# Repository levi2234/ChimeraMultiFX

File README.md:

# ChimeraMultiFX

ChimeraMultiFX is a dual-MCU effects pedal platform. The Daisy Seed handles audio DSP while the ESP32 manages controls, Wi-Fi, and the browser-based UI.

## Repository layout

- [firmware/daisy](firmware/daisy) — Daisy Seed firmware built with libDaisy and DaisySP
- [firmware/esp32](firmware/esp32) — ESP32 control firmware and LittleFS web UI host
- [frontend](frontend) — Preact/Vite touch interface source
- [hardware/boards](hardware/boards) — KiCad PCB and schematic files
- [docs](docs) — repository notes and debugging write-ups

## Quick start

1. Review [firmware/daisy/README.md](firmware/daisy/README.md) for DSP build and flash steps.
2. Review [firmware/esp32/README.md](firmware/esp32/README.md) for ESP32 build, upload, and Wi-Fi setup.
3. Review [frontend/README.md](frontend/README.md) for local UI development.
4. Open [hardware/boards/daisyBoard.kicad_pro](hardware/boards/daisyBoard.kicad_pro) when working on hardware.

## Uploading code

- Daisy Seed: build with the Daisy make targets, then enter DFU bootloader mode and run the flashing command from [firmware/daisy/README.md](firmware/daisy/README.md).
- ESP32: build and upload from PlatformIO with the commands in [firmware/esp32/README.md](firmware/esp32/README.md).
- Frontend UI: build the web assets and upload them to the ESP32 filesystem using the steps in [frontend/README.md](frontend/README.md).

## Notes

- The ESP32 serves the built frontend from its LittleFS data partition.
- The Daisy and ESP32 communicate over UART; the ESP32 exposes a small HTTP/WebSocket bridge for the UI.

## License

MIT — see [LICENSE](LICENSE).

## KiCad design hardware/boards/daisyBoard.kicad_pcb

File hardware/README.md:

# Hardware Development

This directory contains all Electronic Design Automation (EDA) files, schematics, Bill of Materials (BOMs), and mechanical designs (enclosures, 3D models) for the ChimeraMultiFX pedal.

## Modular Board System

The hardware is designed to be modular and stackable:
- **`boards/audio-daisy/`**: The main audio DSP board housing the Daisy Seed.
- **`boards/control-esp32/`**: The controller board housing the ESP32 and inputs.
- **`boards/frontend-rpi/`**: The display driver board for the Raspberry Pi and 7" touchscreen.
- **`boards/power-supply/`**: Clean power delivery and distribution for the stack.

## Structure

- **`boards/`**: Contains the EDA project files (e.g., KiCad/Altium) as well as the exported PDF schematics for each specific PCB. Keeping the schematics in their respective board folders ensures that the design files and their documentation are tightly coupled.
- **`mechanical/`**: Contains STEP files, 3D models for the enclosure, and faceplate designs.

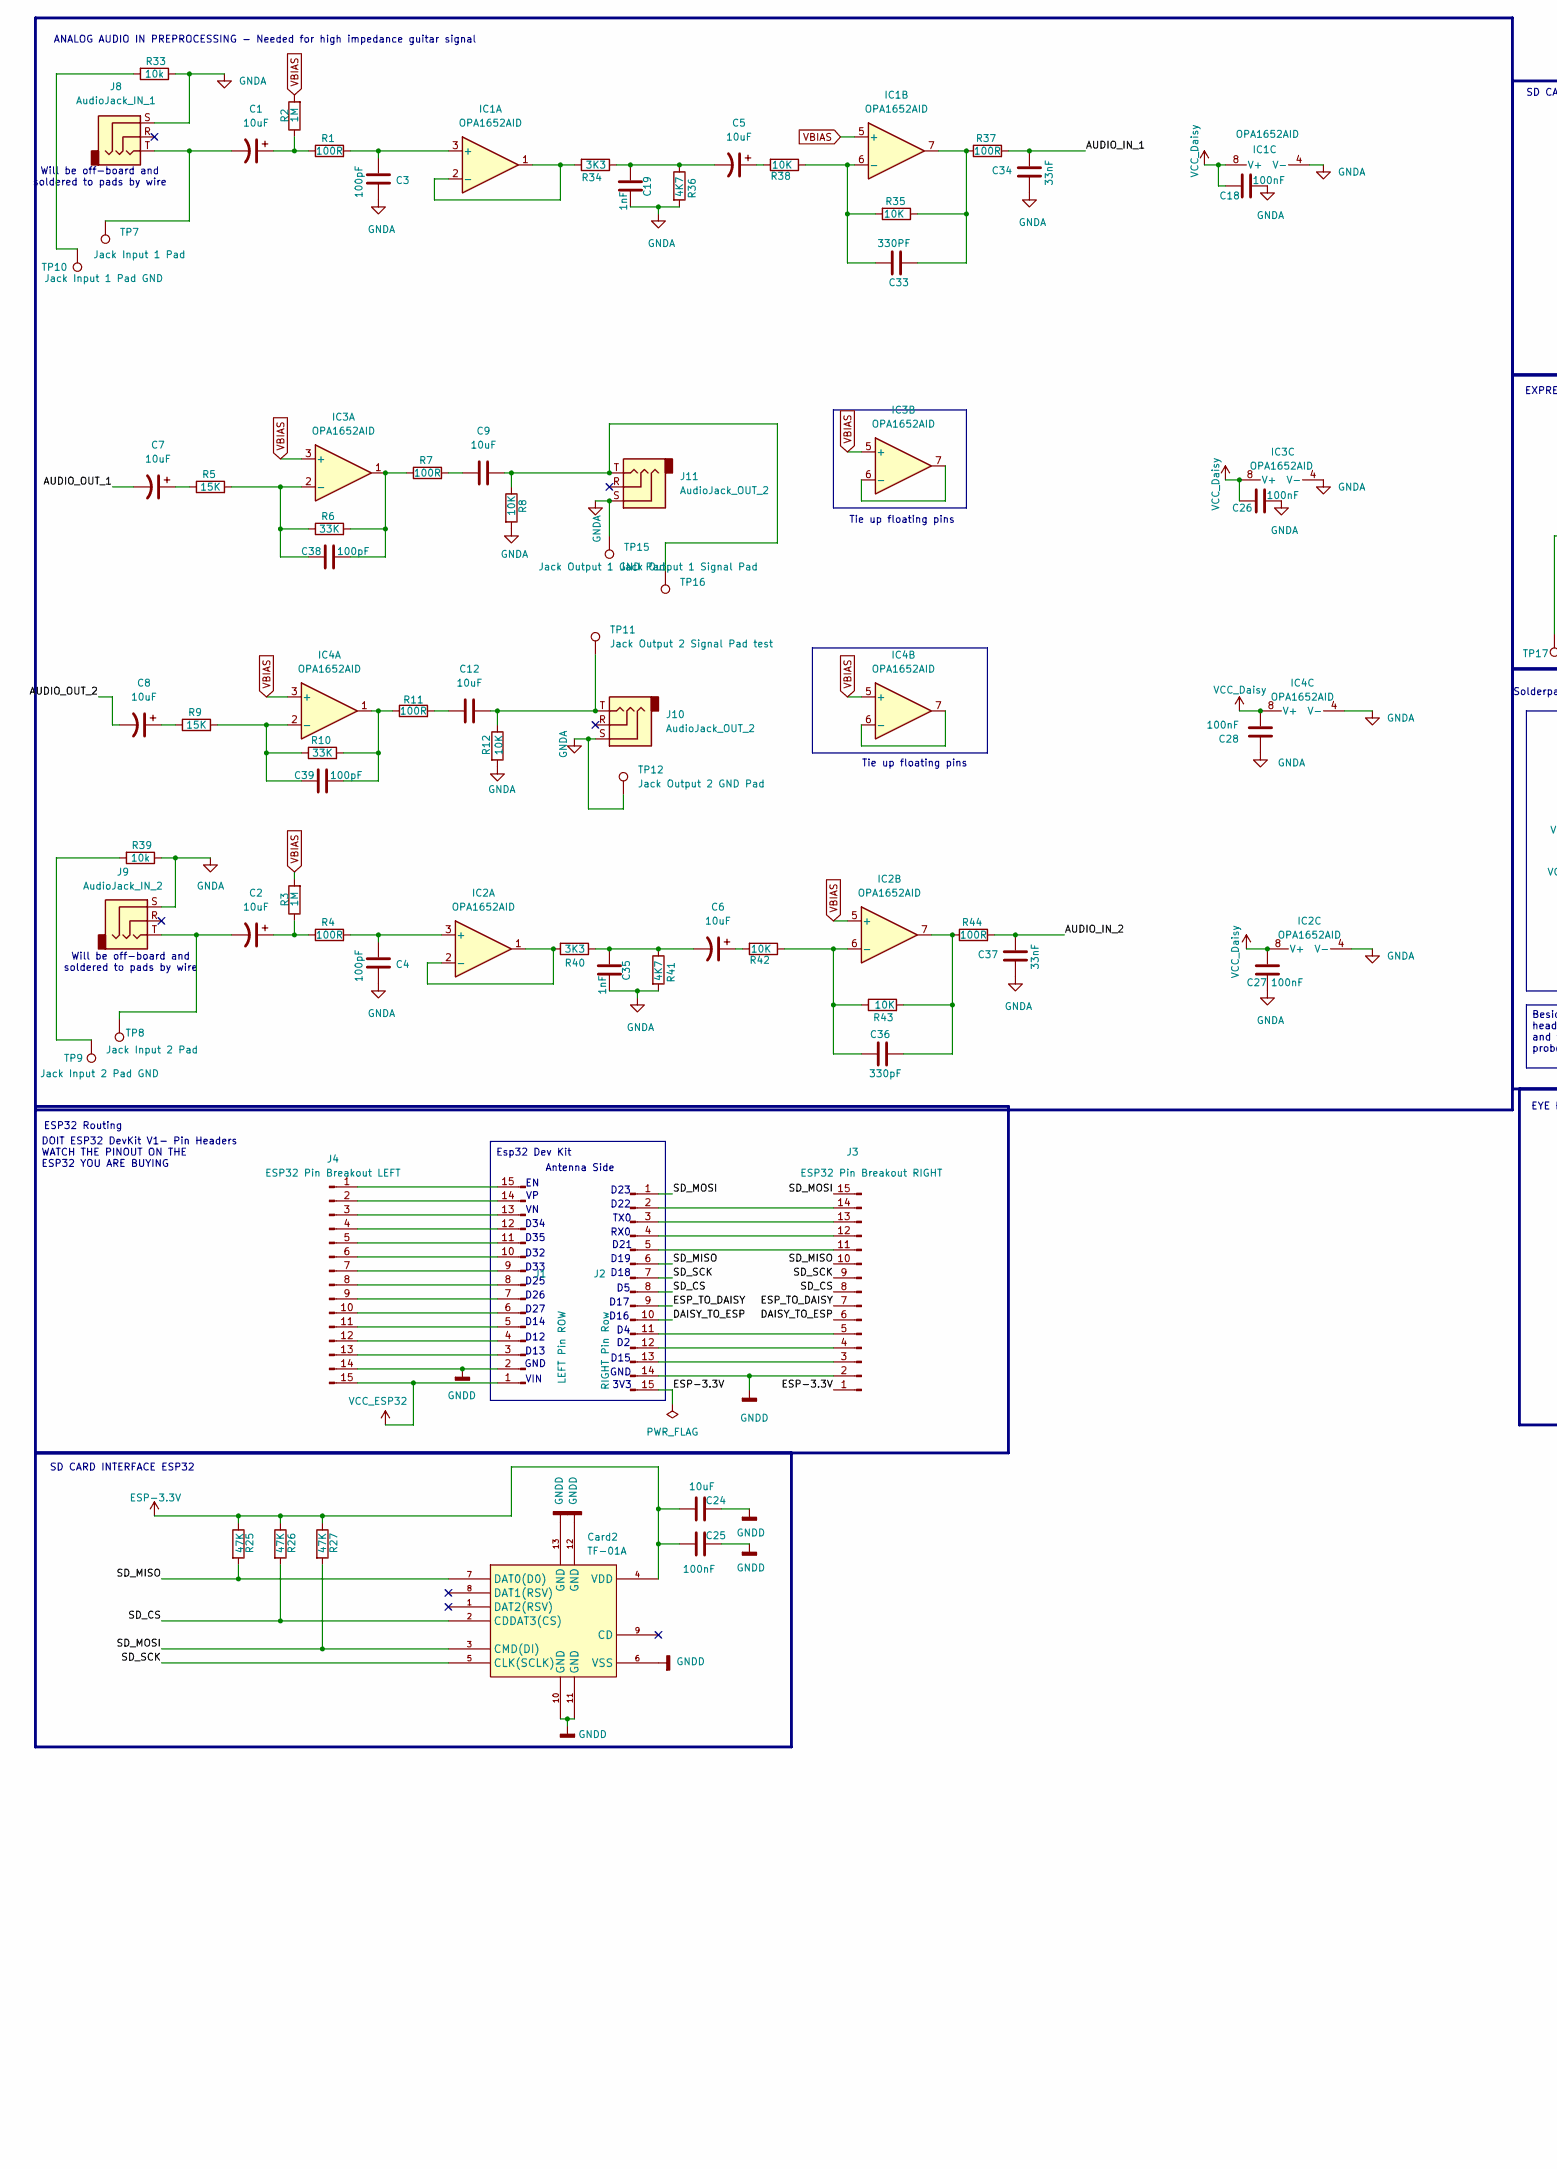
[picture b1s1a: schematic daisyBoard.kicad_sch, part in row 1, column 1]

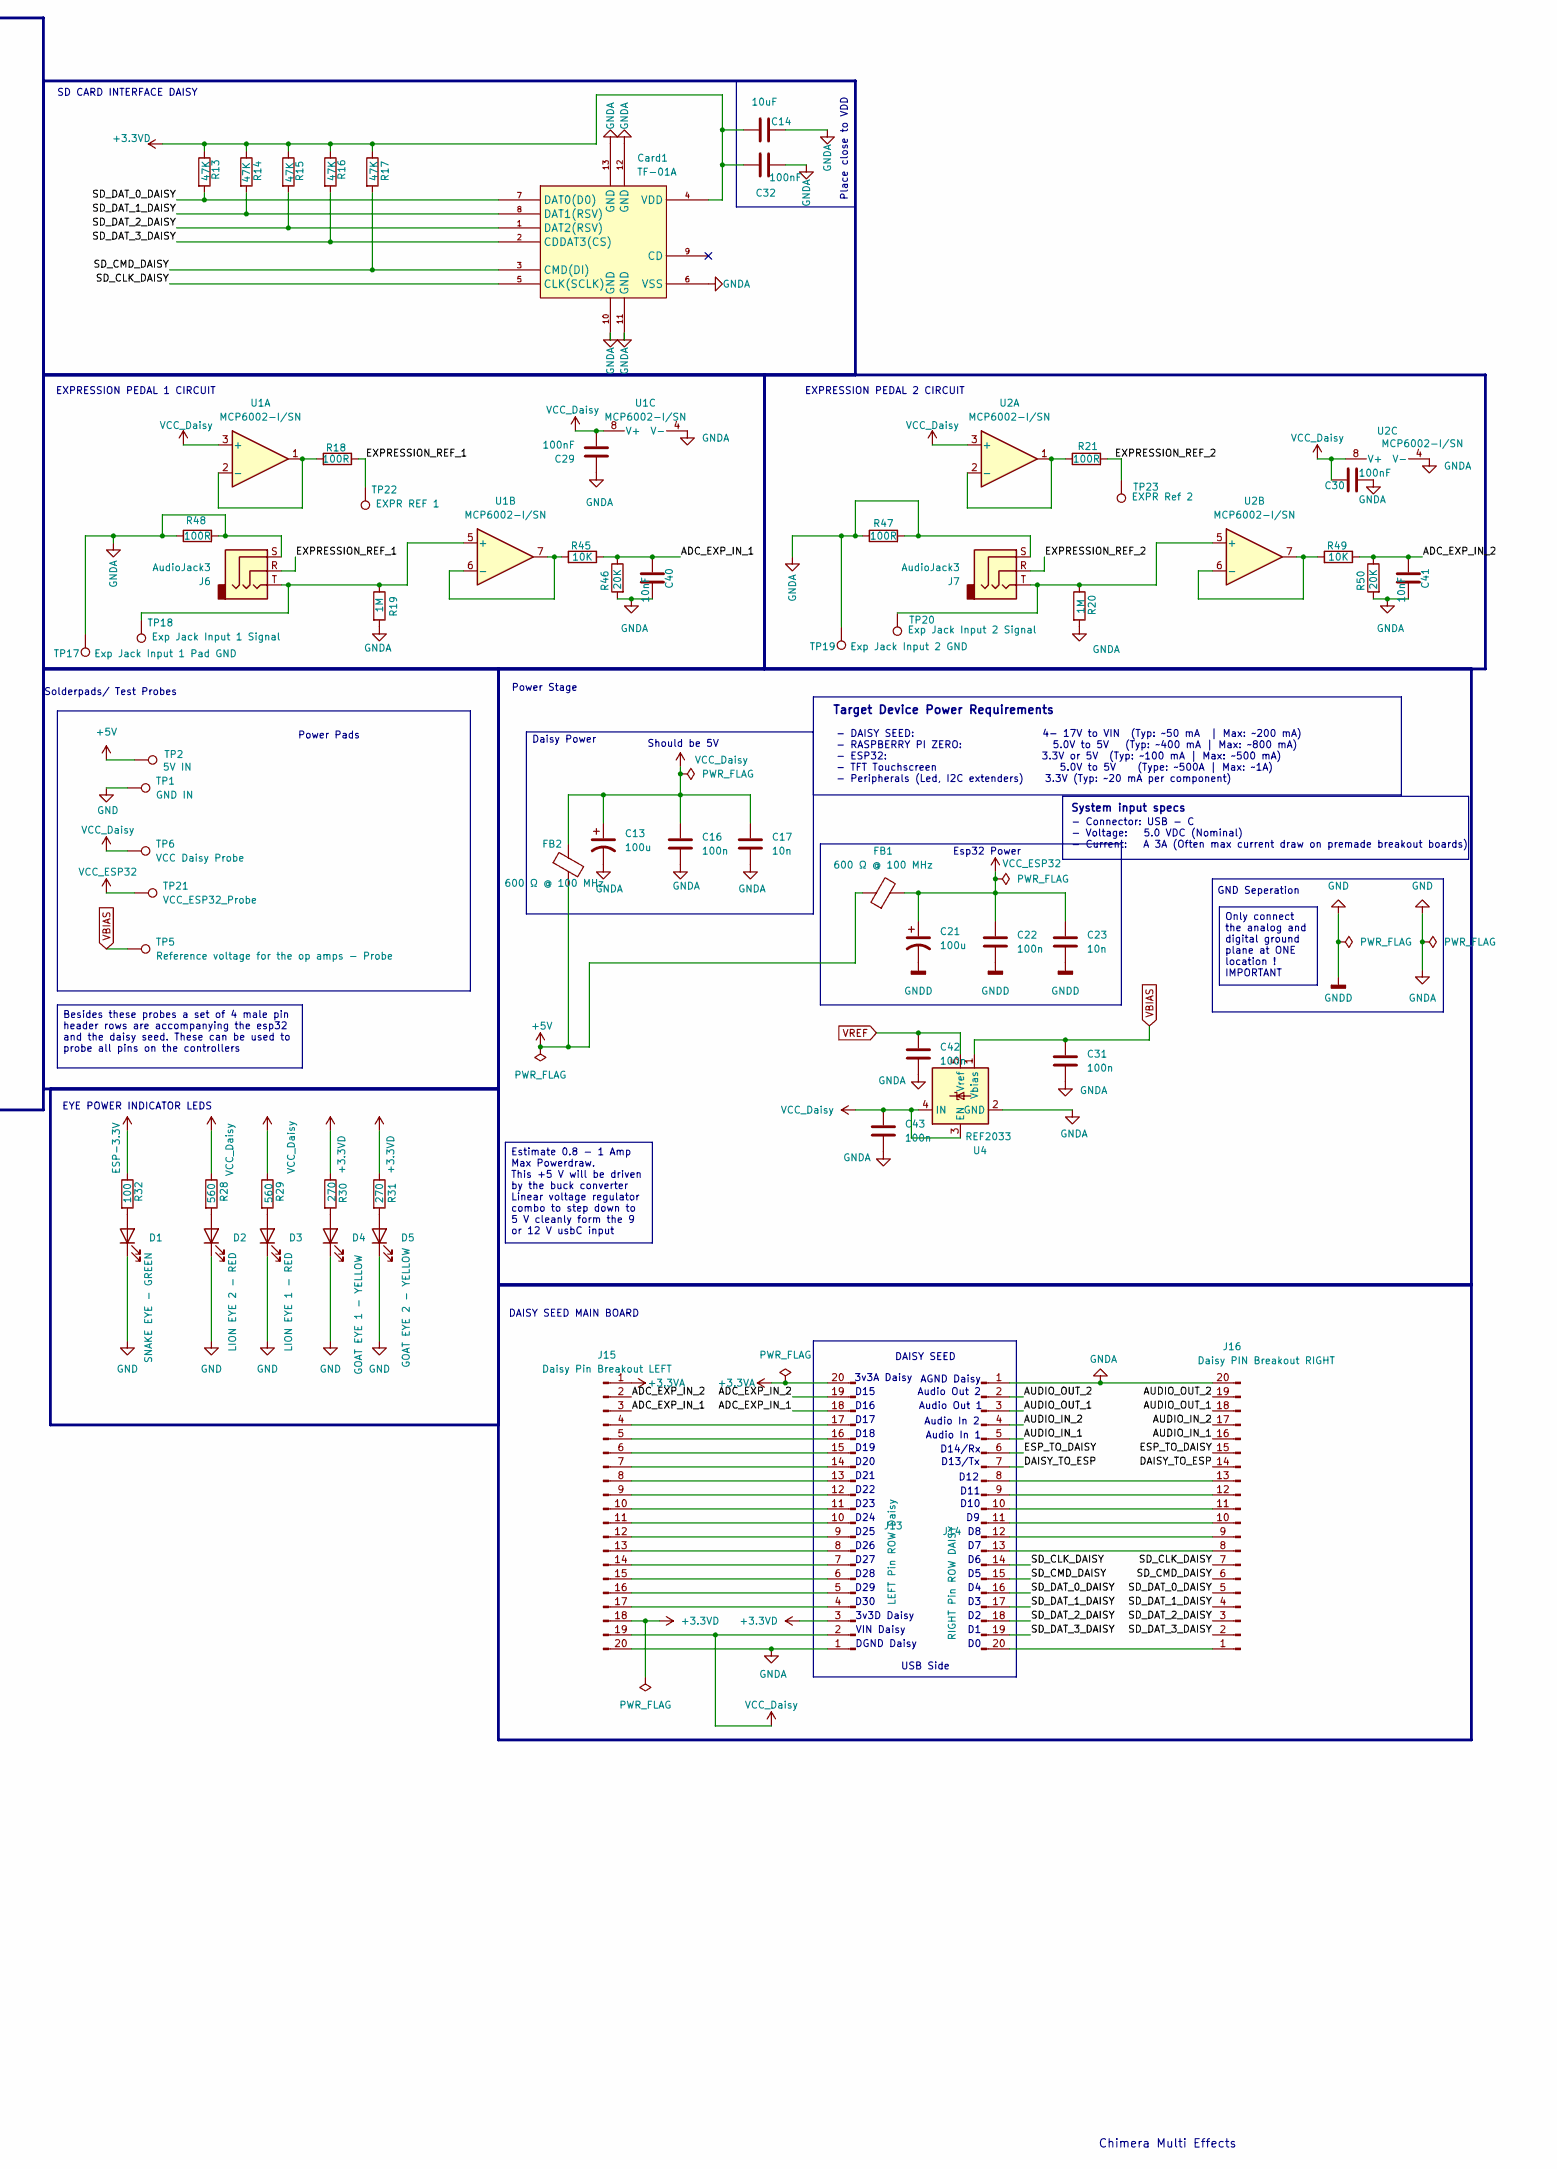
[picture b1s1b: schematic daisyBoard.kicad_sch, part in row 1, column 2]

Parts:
C1, C2, C5, C6, C7, C8, C9, C12, C14, C24: 10uF; C_0805_2012Metric
C3, C4, C38, C39: 100pF; C_0603_1608Metric
C13: 100u; C_0603_1608Metric
C16, C22, C31, C42, C43: 100n; C_0603_1608Metric
C17, C23: 10n; C_0603_1608Metric
C18, C25, C26, C27, C28, C29, C30, C32: 100nF; C_0603_1608Metric
C19, C35: 1nF; C_0603_1608Metric
C21: 100u; C_0805_2012Metric
C33: 330PF; C_0603_1608Metric
C34, C37: 33nF; C_0603_1608Metric
C36: 330pF; C_0603_1608Metric
C40, C41: 10nF; C_0603_1608Metric
Card1, Card2: TF-01A; C91145_TF-SMD_TF-01A; LCSC C91145
D1: SNAKE EYE - GREEN; LED_0201_0603Metric
D2: LION EYE 2 - RED; LED_0201_0603Metric
D3: LION EYE 1 - RED; LED_0201_0603Metric
D4: GOAT EYE 1 - YELLOW; LED_0201_0603Metric
D5: GOAT EYE 2 - YELLOW; LED_0201_0603Metric
FB1, FB2: 600 Ω @ 100 MHz; L_0805_2012Metric
IC1, IC2, IC3, IC4: OPA1652AID; SOIC-8_3.9x4.9mm_P1.27mm
J1: LEFT Pin ROW; PinSocket_1x15_P2.54mm_Vertical
J2: RIGHT Pin Row; PinSocket_1x15_P2.54mm_Vertical
J3: ESP32 Pin Breakout RIGHT; PinHeader_1x15_P2.54mm_Vertical
J4: ESP32 Pin Breakout LEFT; PinHeader_1x15_P2.54mm_Vertical
J6, J7: AudioJack3
J8: AudioJack_IN_1
J9: AudioJack_IN_2
J10, J11: AudioJack_OUT_2
J13: LEFT Pin ROW Daisy; PinSocket_1x20_P2.54mm_Vertical
J14: RIGHT Pin ROW DAISY; PinSocket_1x20_P2.54mm_Vertical
J15: Daisy Pin Breakout LEFT; PinHeader_1x20_P2.54mm_Vertical
J16: Daisy PIN Breakout RIGHT; PinHeader_1x20_P2.54mm_Vertical
R1, R4, R7, R11, R18, R21, R37, R44, R47, R48: 100R; R_0603_1608Metric
R2, R3, R19, R20: 1M; R_0603_1608Metric
R5, R9: 15K; R_0603_1608Metric
R6, R10: 33K; R_0603_1608Metric
R8, R12, R35, R38, R42, R43, R45, R49: 10K; R_0603_1608Metric
R13, R14, R15, R16, R17, R25, R26, R27: 47K; R_0603_1608Metric
R28, R29: 560; R_0603_1608Metric
R30, R31: 270; R_0603_1608Metric
R32: 100; R_0603_1608Metric
R33, R39: 10k; R_0603_1608Metric
R34, R40: 3K3; R_0603_1608Metric
R36, R41: 4K7; R_0603_1608Metric
R46, R50: 20K; R_0603_1608Metric
TP1: GND IN; TestPoint_THTPad_D2.5mm_Drill1.2mm
TP2: 5V IN; TestPoint_THTPad_D2.5mm_Drill1.2mm
TP5: Reference voltage for the op amps - Probe; TestPoint_Pad_2.0x2.0mm
TP6: VCC Daisy Probe; TestPoint_Pad_2.0x2.0mm
TP7: Jack Input 1 Pad; TestPoint_THTPad_D2.5mm_Drill1.2mm
TP8: Jack Input 2 Pad; TestPoint_THTPad_D2.5mm_Drill1.2mm
TP9: Jack Input 2 Pad GND; TestPoint_THTPad_D2.5mm_Drill1.2mm
TP10: Jack Input 1 Pad GND; TestPoint_THTPad_D2.5mm_Drill1.2mm
TP11: Jack Output 2 Signal Pad test; TestPoint_THTPad_D2.5mm_Drill1.2mm
TP12: Jack Output 2 GND Pad; TestPoint_THTPad_D2.5mm_Drill1.2mm
TP15: Jack Output 1 GND Pad; TestPoint_THTPad_D2.5mm_Drill1.2mm
TP16: Jack Output 1 Signal Pad; TestPoint_THTPad_D2.5mm_Drill1.2mm
TP17: Exp Jack Input 1 Pad GND; TestPoint_THTPad_D2.5mm_Drill1.2mm
TP18: Exp Jack Input 1 Signal; TestPoint_THTPad_D2.5mm_Drill1.2mm
TP19: Exp Jack Input 2 GND; TestPoint_THTPad_D2.5mm_Drill1.2mm
TP20: Exp Jack Input 2 Signal; TestPoint_THTPad_D2.5mm_Drill1.2mm
TP21: VCC_ESP32_Probe; TestPoint_Pad_2.0x2.0mm
TP22: EXPR REF 1; TestPoint_THTPad_D2.5mm_Drill1.2mm
TP23: EXPR Ref 2; TestPoint_THTPad_D2.5mm_Drill1.2mm
U1, U2: MCP6002-I/SN; SOIC-8_3.9x4.9mm_P1.27mm
U4: REF2033; SOT-23-5

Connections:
+3.3VA: J13.20, J15.1
+3.3VD: C14.2, C32.2, Card1.4 (VDD), J13.3, J15.18, R13.1, R14.1, R15.1, R16.1, R17.1, R30.1, R31.1
+5V: FB1.1, FB2.2, TP2.1 (1_1)
/ADC_EXP_IN_1: C40.2, J13.18, J15.3, R45.1, R46.1
/ADC_EXP_IN_2: C41.2, J13.19, J15.2, R49.1, R50.1
/AUDIO_IN_1: C34.1, J14.5, J16.16, R37.2
/AUDIO_IN_2: C37.1, J14.4, J16.17, R44.2
/AUDIO_OUT_1: C7.2, J14.3, J16.18
/AUDIO_OUT_2: C8.2, J14.2, J16.19
/DAISY_TO_ESP: J2.10, J3.6, J14.7, J16.14
/ESP_TO_DAISY: J2.9, J3.7, J14.6, J16.15
/EXPRESSION_REF_1: J6.R, R18.1, TP22.1 (1_1)
/EXPRESSION_REF_2: J7.R, R21.2, TP23.1 (1_1)
/SD_CLK_DAISY: Card1.5 (CLK(SCLK)), J14.14, J16.7
/SD_CMD_DAISY: Card1.3 (CMD(DI)), J14.15, J16.6, R17.2
/SD_CS: Card2.2 (CDDAT3(CS)), J2.8, J3.8, R26.2
/SD_DAT_0_DAISY: Card1.7 (DAT0(D0)), J14.16, J16.5, R13.2
/SD_DAT_1_DAISY: Card1.8 (DAT1(RSV)), J14.17, J16.4, R14.2
/SD_DAT_2_DAISY: Card1.1 (DAT2(RSV)), J14.18, J16.3, R15.2
/SD_DAT_3_DAISY: Card1.2 (CDDAT3(CS)), J14.19, J16.2, R16.2
/SD_MISO: Card2.7 (DAT0(D0)), J2.6, J3.10, R25.2
/SD_MOSI: Card2.3 (CMD(DI)), J2.1, J3.15, R27.2
/SD_SCK: Card2.5 (CLK(SCLK)), J2.7, J3.9
ESP-3.3V: C24.2, C25.2, Card2.4 (VDD), J2.15, J3.1, R25.1, R26.1, R27.1, R32.1
GND: C3.1, C4.1, C13.2, C14.1, C16.2, C17.2, C18.1, C19.1, C21.2, C22.2, C23.2, C24.1, C25.1, C26.1, C27.1, C28.1, C29.1, C30.2, C31.1, C32.1, C34.2, C35.1, C37.2, C40.1, C41.1, C42.1, C43.1, Card1.6 (VSS), Card1.10 (GND), Card1.11 (GND), Card1.12 (GND), Card1.13 (GND), Card2.6 (VSS), Card2.10 (GND), Card2.11 (GND), Card2.12 (GND), Card2.13 (GND), D1.1 (K), D2.1 (K), D3.1 (K), D4.1 (K), D5.1 (K), IC1.4 (V-), IC2.4 (V-), IC3.4 (V-), IC4.4 (V-), J1.2, J2.14, J3.2, J4.14, J6.S, J7.S, J8.S, J9.S, J10.S, J11.S, J13.1, J14.1, J15.20, J16.20, R8.2, R12.2, R19.2, R20.2, R33.1, R36.2, R39.1, R41.2, R46.2, R47.1, R47.2, R48.1, R48.2, R50.2, TP1.1 (1_1), TP12.1 (1_1), TP15.1 (1_1), TP17.1 (1_1), TP19.1 (1_1), U1.4 (V-), U2.4 (V-), U4.2 (GND)
unnamed: C1.1, R1.1, R2.1
unnamed: C1.2, J8.T, TP7.1 (1_1)
unnamed: C2.1, R3.1, R4.1
unnamed: C2.2, J9.T, TP8.1 (1_1)
unnamed: C5.1, R38.2
unnamed: C6.1, R42.2
unnamed: C7.1, R5.1
unnamed: C8.1, R9.1
unnamed: C9.1, R7.2
unnamed: C9.2, J11.T, R8.1, TP16.1 (1_1)
unnamed: C12.1, R11.2
unnamed: C12.2, J10.T, R12.1, TP11.1 (1_1)
unnamed: C5.2, C19.2, R34.1, R36.1
unnamed: C33.2, IC1.7, R35.1, R37.1
unnamed: C6.2, C35.2, R40.1, R41.1
unnamed: C36.1, IC2.7, R43.2, R44.1
unnamed: C38.2, IC3.1, R6.2, R7.1
unnamed: C39.2, IC4.1, R10.2, R11.1
unnamed: D1.2 (A), R32.2
unnamed: D2.2 (A), R28.2
unnamed: D3.2 (A), R29.2
unnamed: D4.2 (A), R30.2
unnamed: D5.2 (A), R31.2
unnamed: C3.2, IC1.3 (+), R1.2
unnamed: IC1.1, IC1.2 (-), R34.2
unnamed: C33.1, IC1.6 (-), R35.2, R38.1
unnamed: C4.2, IC2.3 (+), R4.2
unnamed: IC2.1, IC2.2 (-), R40.2
unnamed: C36.2, IC2.6 (-), R42.1, R43.1
unnamed: C38.1, IC3.2 (-), R5.2, R6.1
unnamed: IC3.6 (-), IC3.7
unnamed: C39.1, IC4.2 (-), R9.2, R10.1
unnamed: IC4.6 (-), IC4.7
unnamed: J1.3, J4.13
unnamed: J1.4, J4.12
unnamed: J1.5, J4.11
unnamed: J1.6, J4.10
unnamed: J1.7, J4.9
unnamed: J1.8, J4.8
unnamed: J1.9, J4.7
unnamed: J1.10, J4.6
unnamed: J1.11, J4.5
unnamed: J1.12, J4.4
unnamed: J1.13, J4.3
unnamed: J1.14, J4.2
unnamed: J1.15, J4.1
unnamed: J2.2, J3.14
unnamed: J2.3, J3.13
unnamed: J2.4, J3.12
unnamed: J2.5, J3.11
unnamed: J2.11, J3.5
unnamed: J2.12, J3.4
unnamed: J2.13, J3.3
unnamed: J13.4, J15.17
unnamed: J13.5, J15.16
unnamed: J13.6, J15.15
unnamed: J13.7, J15.14
unnamed: J13.8, J15.13
unnamed: J13.9, J15.12
unnamed: J13.10, J15.11
unnamed: J13.11, J15.10
unnamed: J13.12, J15.9
unnamed: J13.13, J15.8
unnamed: J13.14, J15.7
unnamed: J13.15, J15.6
unnamed: J13.16, J15.5
unnamed: J13.17, J15.4
unnamed: J14.8, J16.13
unnamed: J14.9, J16.12
unnamed: J14.10, J16.11
unnamed: J14.11, J16.10
unnamed: J14.12, J16.9
unnamed: J14.13, J16.8
unnamed: J14.20, J16.1
unnamed: R33.2, TP10.1 (1_1)
unnamed: R39.2, TP9.1 (1_1)
unnamed: R18.2, U1.1, U1.2 (-)
unnamed: J6.T, R19.1, TP18.1 (1_1), U1.5 (+)
unnamed: R45.2, U1.6 (-), U1.7
unnamed: R21.1, U2.1, U2.2 (-)
unnamed: J7.T, R20.1, TP20.1 (1_1), U2.5 (+)
unnamed: R49.2, U2.6 (-), U2.7
VBIAS: C31.2, IC1.5 (+), IC2.5 (+), IC3.3 (+), IC3.5 (+), IC4.3 (+), IC4.5 (+), R2.2, R3.2, TP5.1 (1_1), U4.1 (Vbias)
VCC_Daisy: C13.1, C16.1, C17.1, C18.2, C26.2, C27.2, C28.2, C29.2, C30.1, C43.2, FB2.1, IC1.8 (V+), IC2.8 (V+), IC3.8 (V+), IC4.8 (V+), J13.2, J15.19, R28.1, R29.1, TP6.1 (1_1), U1.3 (+), U1.8 (V+), U2.3 (+), U2.8 (V+), U4.3 (EN), U4.4 (IN)
VCC_ESP32: C21.1, C22.1, C23.1, FB1.2, J1.1, J4.15, TP21.1 (1_1)
VREF: C42.2, U4.5 (Vref)

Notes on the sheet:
Target Device Power Requirements
D34
D23
D33
Tie up floating pins
D14/Rx
D30
D15
D13/Tx
D32
D16
RX0
TX0
GND
D14
D25
Audio Out 1
USB Side
DGND Daisy
DAISY SEED
D21
EYE POWER INDICATOR LEDS
D29
D22
Audio In 2
Power Stage
3v3A Daisy
DOIT ESP32 DevKit V1- Pin Headers WATCH THE PINOUT ON THE ESP32 YOU ARE BUYING
3v3D Daisy
Antenna Side
ESP32 Routing
- DAISY SEED: 4- 17V to VIN (Typ: ~50 mA | Max: ~200 mA) - RASPBERRY PI ZERO: 5.0V to 5V (Typ: ~400 mA | Max: ~800 mA) - ESP32: 3.3V or 5V (Typ: ~100 mA | Max: ~500 mA) - TFT Touchscreen 5.0V to 5V (Type: ~500A | Max: ~1A) - Peripherals (Led, I2C extenders) 3.3V (Typ: ~20 mA per component)
Place close to VDD
D35
SD CARD INTERFACE ESP32
D17
Solderpads/ Test Probes
Audio Out 2
D13
D20

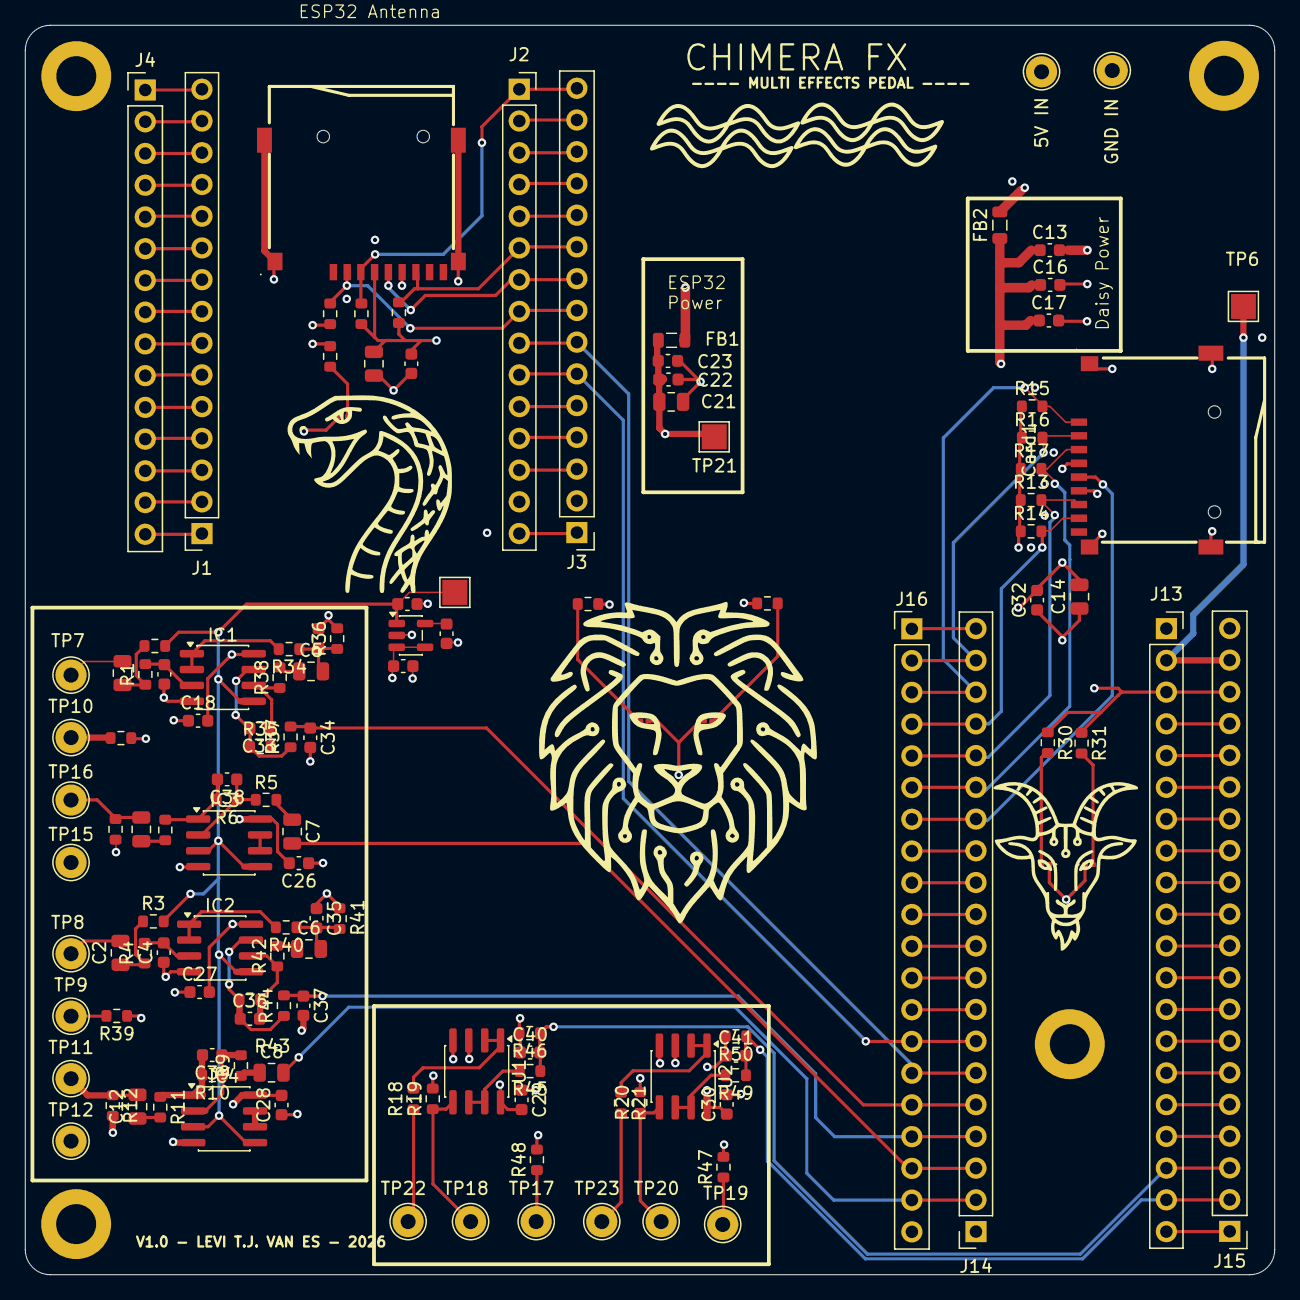
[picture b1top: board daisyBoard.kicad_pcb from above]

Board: 4 copper layers, 100.0 x 100.0 mm, 129 parts (0 on the bottom side), 111 nets.

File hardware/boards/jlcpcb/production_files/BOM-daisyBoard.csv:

Comment,Designator,Footprint,LCSC,Quantity
100,R32,R_0603_1608Metric,C22775,1
100R,"R1,R11,R18,R21,R37,R4,R44,R47,R48,R7",R_0603_1608Metric,C22775,10
100n,"C16,C22,C31,C42,C43",C_0603_1608Metric,C14663,5
100nF,"C18,C25,C26,C27,C28,C29,C30,C32",C_0603_1608Metric,C14663,8
100pF,"C3,C38,C39,C4",C_0603_1608Metric,C14858,4
100u,"C13,C21",C_0603_1608Metric,C15008,2
10K,"R12,R35,R38,R42,R43,R45,R49,R8",R_0603_1608Metric,C25804,8
10k,"R33,R39",R_0603_1608Metric,C25804,2
10n,"C17,C23",C_0603_1608Metric,C57112,2
10nF,"C40,C41",C_0603_1608Metric,C57112,2
10uF,"C1,C12,C14,C2,C24,C5,C6,C7,C8,C9",C_0805_2012Metric,C15850,10
15K,"R5,R9",R_0603_1608Metric,C22809,2
1M,"R19,R2,R20,R3",R_0603_1608Metric,C22935,4
1nF,"C19,C35",C_0603_1608Metric,C1588,2
20K,"R46,R50",R_0603_1608Metric,C4184,2
270,"R30,R31",R_0603_1608Metric,C22966,2
330PF,C33,C_0603_1608Metric,C1664,1
330pF,C36,C_0603_1608Metric,C1664,1
33K,"R10,R6",R_0603_1608Metric,C4216,2
33nF,"C34,C37",C_0603_1608Metric,C21117,2
3K3,"R34,R40",R_0603_1608Metric,C22978,2
47K,"R13,R14,R15,R16,R17,R25,R26,R27",R_0603_1608Metric,C25819,8
4K7,"R36,R41",R_0603_1608Metric,C23162,2
560,"R28,R29",R_0603_1608Metric,C23204,2
600 Ω @ 100 MHz,"FB1,FB2",L_0805_2012Metric,C51018430,2
GOAT EYE 1 - YELLOW,D4,LED_0201_0603Metric,C2287,1
GOAT EYE 2 - YELLOW,D5,LED_0201_0603Metric,C2287,1
LION EYE 1 - RED,D3,LED_0201_0603Metric,C2286,1
LION EYE 2 - RED,D2,LED_0201_0603Metric,C2286,1
MCP6002-I/SN,"U1,U2",SOIC-8_3.9x4.9mm_P1.27mm,C7377,2
OPA1652AID,"IC1,IC2,IC3,IC4",SOIC-8_3.9x4.9mm_P1.27mm,C30025,4
REF2033,U4,SOT-23-5,C440747,1
SNAKE EYE - GREEN,D1,LED_0201_0603Metric,C12065,1
TF-01A,"Card1,Card2",C91145_TF-SMD_TF-01A,C91145,2
ESP32 Pin Breakout LEFT,J4,PinHeader_1x15_P2.54mm_Vertical,,1
ESP32 Pin Breakout RIGHT,J3,PinHeader_1x15_P2.54mm_Vertical,,1

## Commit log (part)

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2026-05-21 Add initial project structure and documentation for ChimeraMultiFX
    - Created README.md with project overview, hardware details, and building instructions.
    - Added .gitignore to exclude build artifacts and IDE files.
    - Initialized Makefile and source files for Daisy and ESP32 firmware.
    - Created requirements.txt for Pi Zero software dependencies.
    - Implemented main entry point for Pi Zero synth software.
2026-06-02 Add new models and libraries for voltage regulators and operational amplifiers
    - Created new symbol files for LM7805, LM7812, LM7815, and LM7905 voltage regulators.
    - Added TL072 operational amplifier macromodel subcircuit.
    - Introduced a new library file 'regulators.lib' containing SPICE models for the above regulators.
    - Added reference material for the Terrarium Platform, including a parts list, schematic, wiring diagram, and drill template.
    - Included mechanical design assets for the ChimeraMultiFX pedal.
    - Established a software directory structure with README files for web UI and Raspberry Pi kiosk setup.
2026-06-04 feat: update audio-daisy board schematic and add custom footprint library
2026-06-29 bookkeeping
2026-06-29 removed software
2026-06-29 More bookkeeping
2026-06-29 feat: initialize Daisy firmware build system, project documentation, and license files
2026-06-29 feat: implement effect framework with Delay and Distortion effects
2026-06-30 feat: add new effects including Bitcrusher, TanhDistortion, Chorus, Tremolo, Compressor, LowPass, and Delay; update effect chain in main
